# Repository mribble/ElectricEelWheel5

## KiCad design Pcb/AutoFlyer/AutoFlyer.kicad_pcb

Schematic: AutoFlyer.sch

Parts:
C1, C2, C3: 10uF; C_1206
C5: 0.1uF; C_0603
D1: LED_ALT; LED_0805
D3: D_Schottky; D_SOD-523
J1: Screw_Terminal_1x02; Socket_Strip_Straight_1x02_Pitch2.54mm
J2: Programmer; Socket_Strip_Straight_1x06_Pitch2.54mm
J3: Battery; Socket_Strip_Straight_1x04_Pitch2.54mm
R1: 1K; R_0603
R2: 10K; R_0603
R3: 0.5; R_0805
SW1: SW_Push; SW_SPST_PTS645
U1: ATTINY44-20SSU; SOIC-14_3.9x8.7mm_Pitch1.27mm
U2: LD1117S33TR_SOT223; SOT-23
U3: H-Bridge-DMHC3025LSD; SOIC-8-N
X1, X2: HOLE; HOLE_3.0mm

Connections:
+3V3: C2.1, C5.1, J2.3, SW1.2, U1.1 (VCC), U2.2 (VO)
+6V: C3.1, D3.2, J3.4, U3.7
/MotorA: J1.1, U3.2
/MotorB: J1.2, U3.6
/c0: U1.6 ((PCINT7/ICP/OC0B/ADC7)PA7), U3.1
/c1: U1.5 ((PCINT10/CKOUT/OC0A/INT0)PB2), U3.4
/c2: U1.3 ((PCINT9/XTAL2)PB1), U3.5
/c3: U1.2 ((PCINT8/CLKI/XTAL1)PB0), U3.8
/led: D1.2, U1.11 ((PCINT2/AIN1/ADC2)PA2)
/miso: J2.4, U1.8 ((PCINT5/DO/MISO/OC1B/ADC5)PA5)
/mosi: J2.5, U1.7 ((PCINT6/SDA/DI/MOSI/OC1A/ADC6)PA6)
/rst: J2.6, U1.4 ((PCINT11/dW/~RESET~)PB3)
/sck: J2.2, U1.9 ((PCINT4/USCK/SCL/T1/ADC4)PA4)
/shunt: R3.1, U1.13 ((PCINT0/AREF/ADC0)PA0), U3.3
GND: C1.2, C2.2, C3.2, C5.2, J2.1, J3.1, R1.1, R2.1, R3.2, U1.14 (GND), U2.1 (GND)
unnamed: C1.1, D3.1, U2.3 (VI)
unnamed: D1.1, R1.2
unnamed: J3.2, J3.3
unnamed: R2.2, SW1.1, U1.12 ((PCINT1/AIN0/ADC1)PA1)

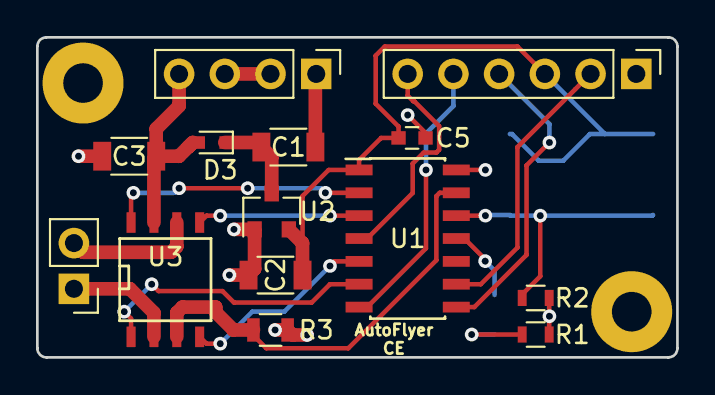
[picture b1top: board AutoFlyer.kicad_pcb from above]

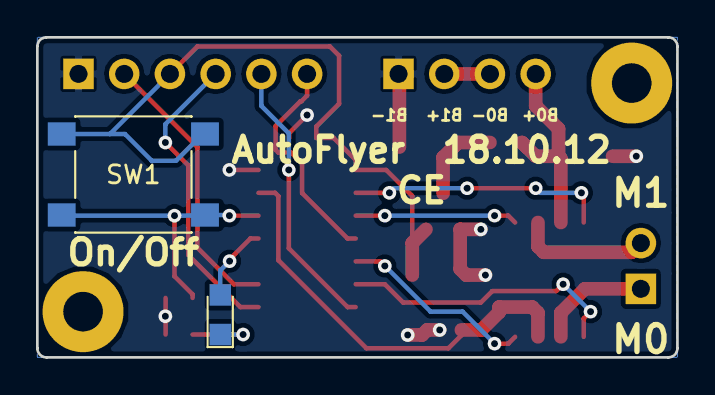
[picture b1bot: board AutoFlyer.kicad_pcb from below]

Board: 2 copper layers, 35.6 x 17.8 mm, 18 parts (2 on the bottom side), 19 nets.

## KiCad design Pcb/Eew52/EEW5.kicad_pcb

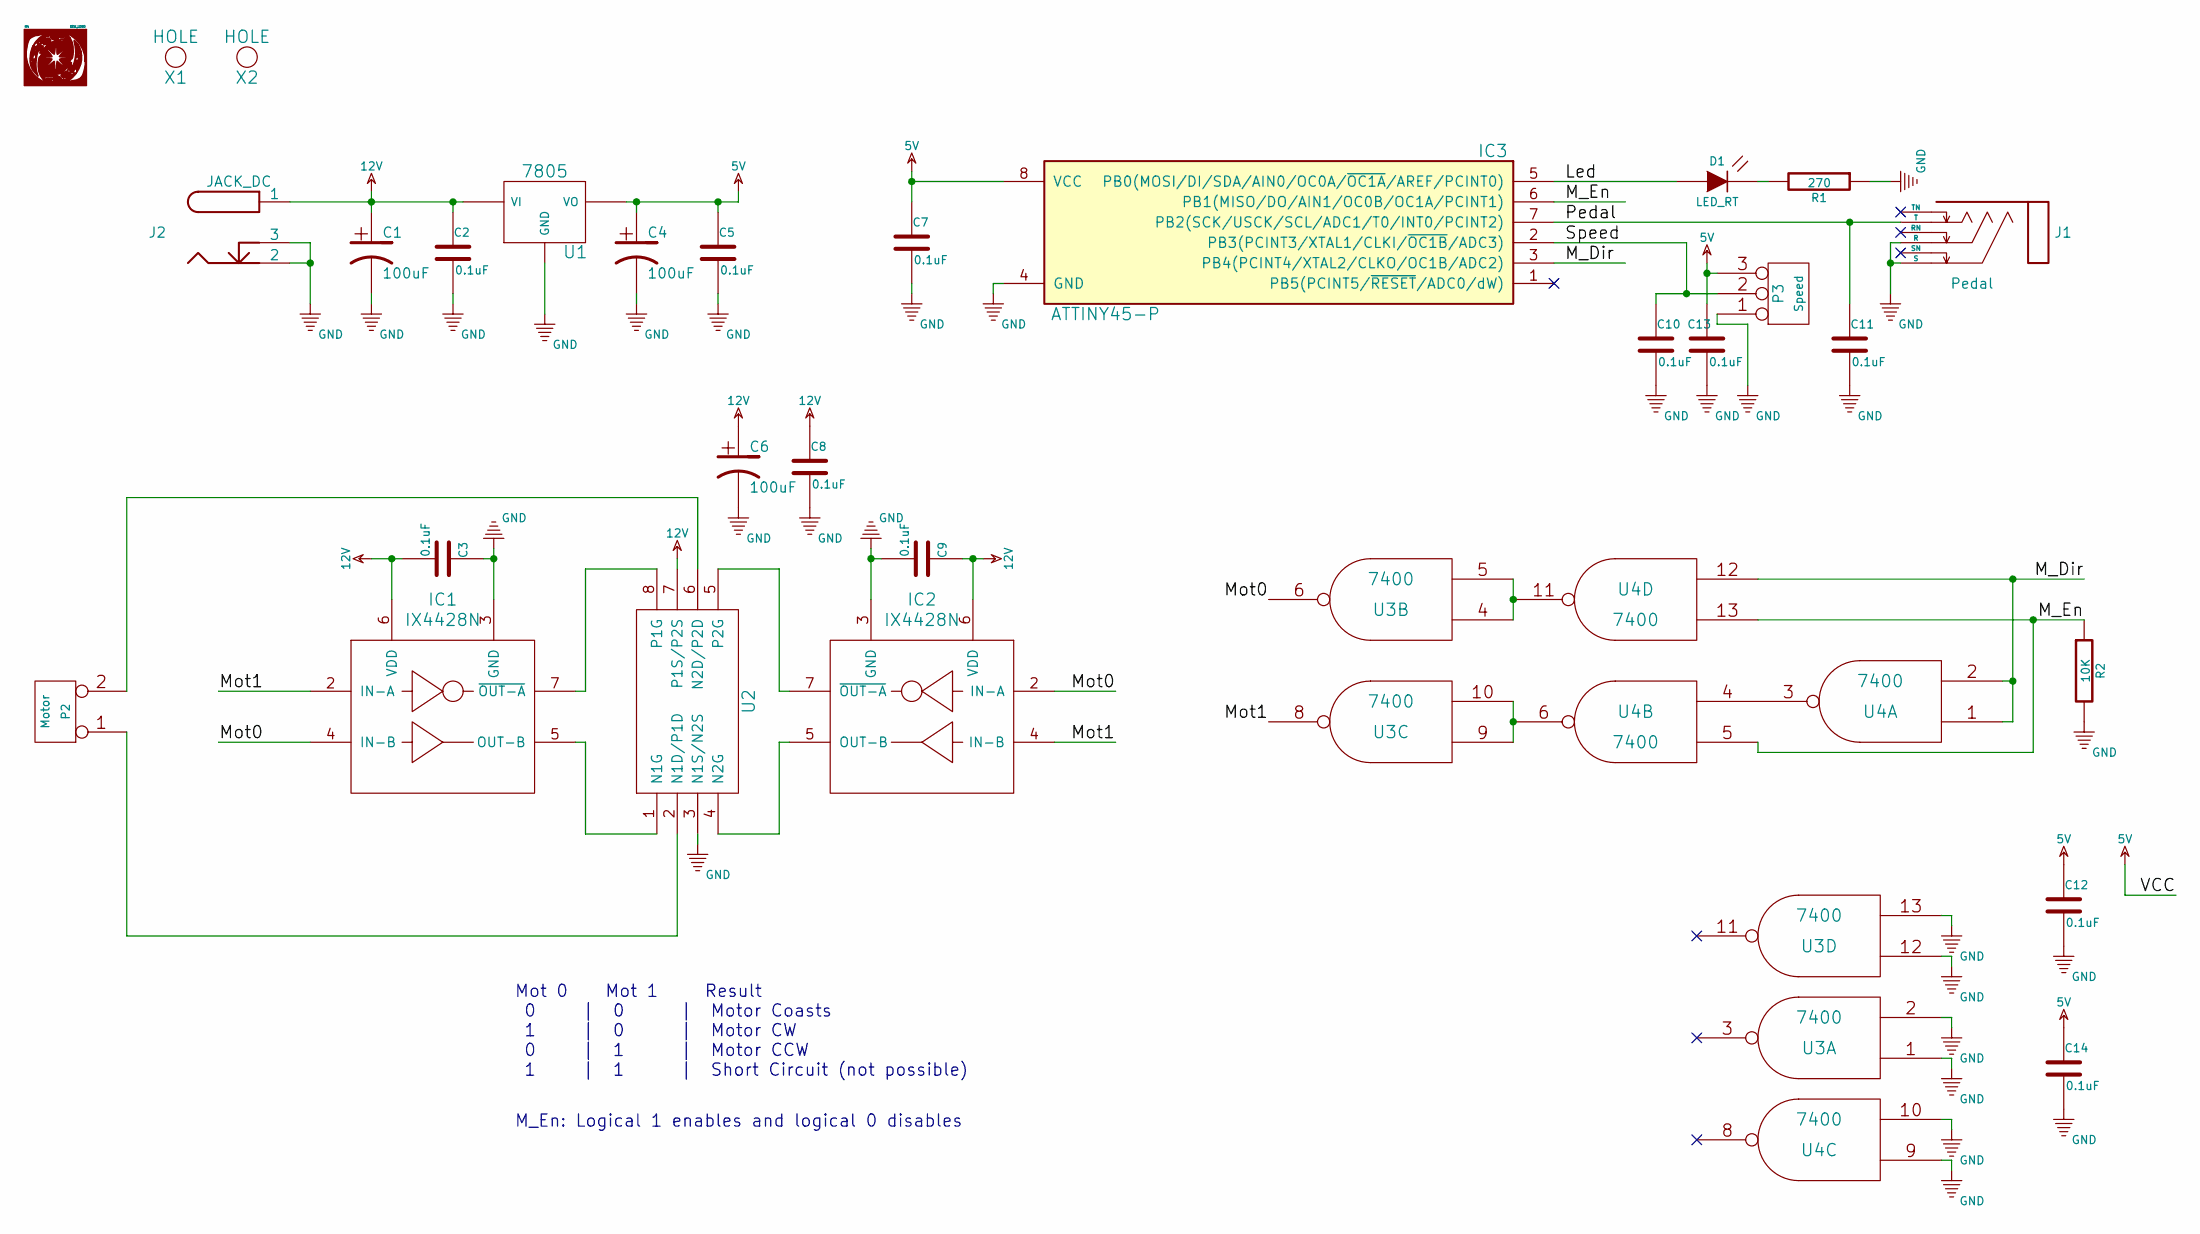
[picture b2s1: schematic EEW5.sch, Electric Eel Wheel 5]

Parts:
C1, C4, C6: 100uF; CP_Elec_6.3x5.7
C2, C3, C5, C7, C8, C9, C10, C11, C12, C13, C14: 0.1uF; C_0603
D1: LED_RT; LED_D5.0mm_Horizontal_O1.27mm_Z3.0mm
H4: EEW_LOGO; ce
IC1, IC2: IX4428N; SOIC-8-N
IC3: ATTINY45-P; DIP-8_W7.62mm_Socket
J1: Pedal; Jack_1_4
J2: JACK_DC; BARREL_JACK
P2: Motor; PhoenixContact_MC-G_02x3.50mm_Angled
P3: Speed; JST_EH_S03B-EH_03x2.50mm_Angled
R1: 270; R_0603
R2: 10K; R_0603
U1: 7805; TO-252-2
U2: H-Bridge-DMHC3025LSD; SOIC-8-N
U3, U4: 7400; SOIC-14_N
X1, X2: HOLE; HOLE_3.0mm

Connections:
5V: C4.1 (Pos), C5.1, C7.1, C12.1, C13.1, C14.1, IC3.8 (VCC), P3.3, U1.3 (VO), U3.14 (VCC), U4.14 (VCC)
12V: C1.1 (Pos), C2.1, C3.2, C6.1 (Pos), C8.1, C9.1, IC1.6 (VDD), IC2.6 (VDD), J2.1, U1.1 (VI), U2.7 (P1S/P2S)
/Led: D1.1 (A), IC3.5 (PB0(MOSI/DI/SDA/AIN0/OC0A/~OC1A~/AREF/P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)
/M_Dir: IC3.3 (PB4(PCINT4/XTAL2/CLKO/OC1B/ADC2)), U4.1, U4.2, U4.12
/M_En: IC3.6 (PB1(MISO/DO/AIN1/OC0B/OC1A/PCINT1)), R2.1, U4.5, U4.13
/Mot0: IC1.4 (IN-B), IC2.2 (IN-A), U3.6
/Mot1: IC1.2 (IN-A), IC2.4 (IN-B), U3.8
/Pedal: C11.1, IC3.7 (PB2(SCK/USCK/SCL/ADC1/T0/INT0/PCINT2)), J1.T
/Speed: C10.1, IC3.2 (PB3(PCINT3/XTAL1/CLKI/~OC1B~/ADC3)), P3.2
GND: C1.2 (Neg), C2.2, C3.1, C4.2 (Neg), C5.2, C6.2 (Neg), C7.2, C8.2, C9.2, C10.2, C11.2, C12.2, C13.2, C14.2, IC1.3 (GND), IC2.3 (GND), IC3.4 (GND), J1.R, J1.S, J2.2, J2.3, P3.1, R1.1, R2.2, U1.2 (GND), U2.3 (N1S/N2S), U3.1, U3.2, U3.7 (GND), U3.12, U3.13, U4.7 (GND), U4.9, U4.10
unnamed: D1.2 (K), R1.2
unnamed: IC1.5 (OUT-B), U2.1 (N1G)
unnamed: IC1.7 (~OUT-A), U2.8 (P1G)
unnamed: IC2.5 (OUT-B), U2.4 (N2G)
unnamed: IC2.7 (~OUT-A), U2.5 (P2G)
unnamed: P2.1, U2.2 (N1D/P1D)
unnamed: P2.2, U2.6 (N2D/P2D)
unnamed: U3.4, U3.5, U4.11
unnamed: U3.9, U3.10, U4.6
unnamed: U4.3, U4.4

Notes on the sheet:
Mot 0 Mot 1 Result 0 | 0 | Motor Coasts 1 | 0 | Motor CW 0 | 1 | Motor CCW 1 | 1 | Short Circuit (not possible)
M_En: Logical 1 enables and logical 0 disables

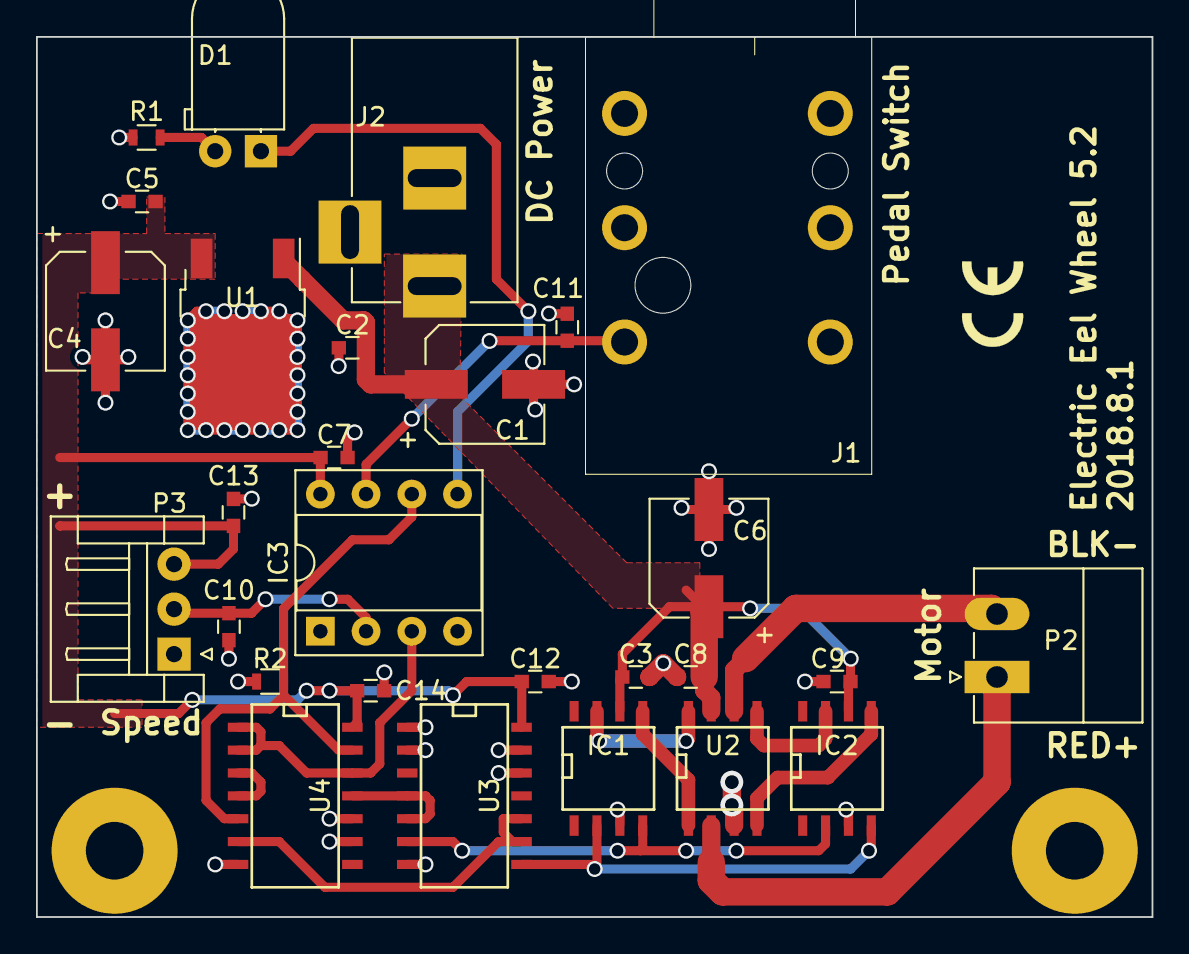
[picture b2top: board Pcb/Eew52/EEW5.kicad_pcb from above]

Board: 2 copper layers, 62.0 x 48.9 mm, 31 parts (0 on the bottom side), 20 nets.

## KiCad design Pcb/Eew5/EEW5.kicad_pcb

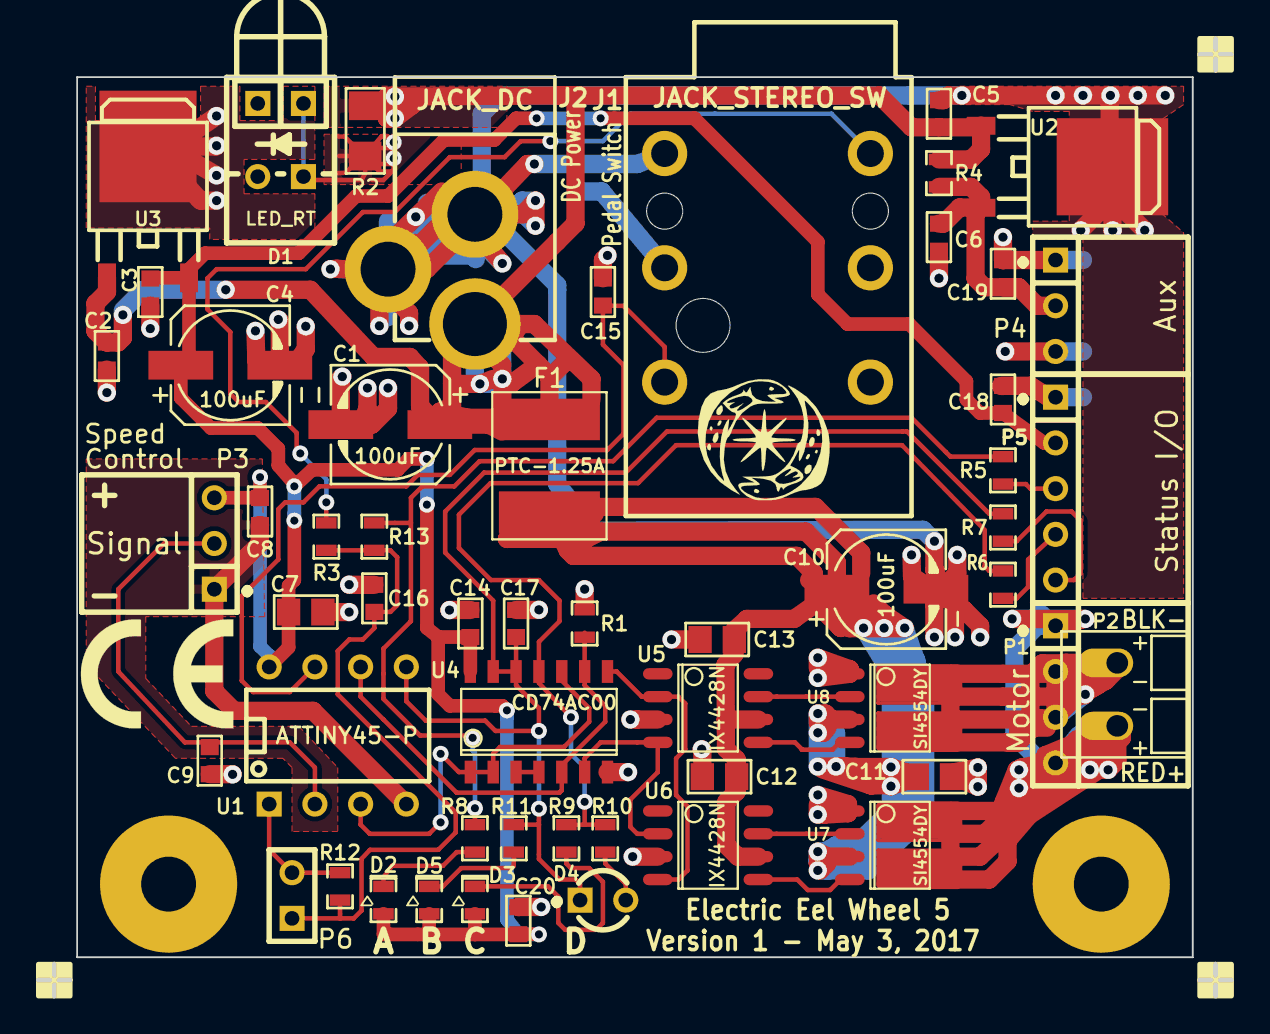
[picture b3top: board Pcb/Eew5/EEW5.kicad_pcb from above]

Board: 2 copper layers, 66.3 x 53.2 mm, 60 parts (0 on the bottom side), 32 nets.

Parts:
C1, C4, C10: 100uF; c_elec_6.3x5.7
C2, C3, C5, C6, C8, C9, C14, C15, C16, C17, C18, C19, C20: 0.1uF; c_0603
C7, C11, C12, C13: 1uF; c_0805
D1: LED_RT; LED_RT_100
D2, D3: Green; SM0603_Diode
D4: R/G; LED_T1_BiPolar_100
D5: Red; SM0603_Diode
F1: PTC-1.25A; PTC_2920
J1: JACK_STEREO_SW; JACK_1-4_STEREO
J2: JACK_DC; JACK_2.1_DC
P1: Motor; SIL-4-RT
P2: Motor; Screw_Terminal_Block_2P
P3: Speed; SIL-3-RT
P4: Aux; SIL-3-RT
P5: Status I/O; SIL-5-RT
P6: R/PE; SIL-2
PS1, PS2: CONN_1; SIL-1
R1: 10k; SM0603_Resistor
R2: 820; r_1206
R3, R4, R12, R13: 0k; SM0603_Resistor
R5, R6, R7, R8, R9, R10, R11: 270; SM0603_Resistor
U1: ATTINY45-P; DIP-8_300
U2: KA78xxE; TO252M
U3: KA7805E; TO252M
U4: CD74AC00; SOIC-14
U5, U6: IX4428N; SOIC-8
U7, U8: SI4554DY; SO-8P2
X1, X2: HOLE; HOLE_4-40
ref***: val***; EEW_Logo_small

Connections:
5V: C3.1, C4.1, C7.1, C8.2, C14.1, C18.1, C20.1, D2.1, D3.1, D5.1, P3.3, P5.2, U1.8, U3.VO, U4.14
/AuxPwr: C6.1, C19.1, P4.2, R4.2, U2.VO
/CCW_LS: U6.7, U7.2
/CW_LS: U5.7, U8.2
/DC_In: C1.1, C2.1, C5.1, F1.2, J2.1, R2.1, R4.1, U2.VI, U3.VI
/HPWR: C10.1, C11.1, C12.2, C13.2, F1.1, U5.6, U6.6, U7.3, U8.3
/M+: P1.1, P1.4, P2.1, U7.5, U7.6, U7.7, U7.8
/M-: P1.2, P1.3, P2.2, U8.5, U8.6, U8.7, U8.8
/M_DIR: U1.3, U4.1, U4.2, U4.10
/M_EN: R1.1, U1.6, U4.5, U4.9
/PEn_x: C16.1, P6.1, R3.1, R12.2, R13.2
/PEn_y: J1.SN, R3.2
/PEn_z: R5.2, R8.1, R13.1
/PedalEnable: P6.2, R12.1, U1.1
/PedalSig: C15.1, J1.T, U1.7
/Speed: C9.2, P3.2, U1.2
/Status: C17.1, D4.1, R7.2, R11.1, U1.5, U4.12, U4.13
/~CCW: U4.6, U5.4, U6.2
/~CCW_HS: U5.5, U8.4
/~CW: U4.8, U5.2, U6.4
/~CW_HS: U6.5, U7.4
/~M_DIR: U4.3, U4.4
/~Status: R6.2, R9.1, R10.1, U4.11
GND: C1.2, C2.2, C3.2, C4.2, C5.2, C6.2, C7.2, C8.1, C9.1, C10.2, C11.2, C12.1, C13.1, C14.2, C15.2, C16.2, C17.2, C18.2, C19.2, C20.2, D1.2, J1.R, J1.S, J2.2, J2.3, P3.1, P4.1, P4.3, P5.1, PS2.1, R1.2, U1.4, U2.GND, U3.GND, U4.7, U5.3, U6.3, U7.1, U8.1
unnamed: D2.2, R8.2
unnamed: P5.4, R6.1
unnamed: D3.2, R9.2
unnamed: D5.2, R11.2
unnamed: D4.2, R10.2
unnamed: D1.1, PS1.1, R2.2
unnamed: P5.3, R5.1
unnamed: P5.5, R7.1

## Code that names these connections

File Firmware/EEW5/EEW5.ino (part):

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// 1.01 Sep 8, 2015 - Nedd
//      - Simplified some math lines to improve loop speed
//      - Increased system clock to 16mhz (was 1mhz). This improves the resolution of the micros() counter, reduces signal jitter, allows faster PWM frequencies.
//      - Added "TESTMODE" for repeated LV programming during testing. (In TESTMODE fuse RSTDISBL is unprogrammed, Reset (pin 1) is open, PB0 (pin 5) is rewired to M_EN, 
//        MOT_EN_PIN & PEDAL_EN_PIN definitions are swapped).
// 1.02 Oct 31, 2015 - Maurice Ribble
//      - Reduced math by pre-caching high and low speed
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//      - Added Fwd/Rev testing for new pcb MOSFET drive system.
//      - Testing of old PWM method using new prototype PCB design, (version 6).
// 1.05 Feb 02, 2016 - Nedd
//      - Added register setups to use direct PWM output on PB1, PWM comes from OC1A signal, PW is adjusted by setting OCR1A (compare A) of timer1.
//      - Added Dead Zone adjustment (expands range where motor is at 0 speed)
//      - Added Slow Zone adjustment (reduces range where motor does not spin)
//      - Added safe mode at first power on. Operator must adjust speed knob up then back to zero to enable motor. Status line toggles detection points
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// Digital/analog pins
#define PIN_STATUS            0    // Green status LED output     -- LOW=On       HIGH=Off
#define PIN_MOT_EN            1    // Enable motor output         -- LOW=Stop     HIGH=Run
#define PIN_PEDAL             2    // Foot pedal switch input     -- LOW=Pressed  HIGH=Not Pressed
#define APIN_SPEED            3    // Speed control dial analog input (ADC3 = PB3)
#define PIN_MOT_DIR           4    // Direction motor output      -- LOW=CCW      HIGH=CW

// Green Status LED
#define LED_ON  LOW
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
// Speed dial related controls
#define DEAD_ZONE 15               // Range close to zero where motor will be forced off
#define SLOW_ZONE 90               // Shift motor's minimum speed faster to get motor spinning at lower speed dial settings
#define T1_MAX_TIME 168            // Used to help set pwm durations, see setPwmParams() for more details

////////////////////////////////////////////////////////////////////////////////////////////////////////////////////////
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}

////////////////////////////////////////////////////////////////////////////////////////////////////////////////////////
// analogReadSpeedDial - Fast readAnalog for the pin connected to the speed dial
//  input   - void
//  return  - 8 bit analog value
////////////////////////////////////////////////////////////////////////////////////////////////////////////////////////
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////////////////////////////////////////////////////////////////////////////////////////////////////////////////////////
inline void motorPwmOff()
{
  TCCR1 &= ~(1<<COM1A1);  TCCR1 &= ~(1<<COM1A0);  //disconnect pwm from PB1
}  

////////////////////////////////////////////////////////////////////////////////////////////////////////////////////////
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inline void motorPwmOn()
{ 
  TCCR1 |= (1<<COM1A1);  
  TCCR1 |= (1<<COM1A0);  //connect pwm to PB1
}

////////////////////////////////////////////////////////////////////////////////////////////////////////////////////////
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  ADCSRA |=  (1<<ADEN)  ;  // 1, ADC Enable
   
  //ADMUX, ADC Mux Seletion Register
  ADMUX |=  (1<<MUX0);   // 1, adc Mux channel (ADMUX bits MUX[3-0], for ADC3(PB3) single ended need "B0011")
  ADMUX |=  (1<<MUX1);   // 1
  ADMUX &= ~(1<<MUX2);   // 0
  ADMUX &= ~(1<<MUX3);   // 0
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}

////////////////////////////////////////////////////////////////////////////////////////////////////////////////////////
// setPwmParams - Sets up PWM parameters for motor.  Must be called before using the pwm from PB1
////////////////////////////////////////////////////////////////////////////////////////////////////////////////////////
void setPwmParams()
{
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  // Disable motor enable pin 
  digitalWrite(PIN_MOT_EN, LOW);

  // Setup pwm registers for output on PB1 using the timer counter 1
  // Temporarily stop counters by setting Timer Sync Mode bit to 1 
  GTCCR |=  (1<<TSM);
  // Place Timer1 into Reset by setting Timer1 Prescaler to 1
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  // set up all 8-bits of TCCR1, (Timer/Counter1 Control Register)
  // set CTC1 to 1,(Clear Timer/Counter on Compare), this will clear timer1 to 0x00 on match of 0CR1C (maxCnt)   
  // set PWM1A to 1, (PWM A enable), this enables pwm based on match of 0CR1A   
  // set COM1A0 & COM1A0 to 3, (compare A output mode), this connects 0C1A to PB1, and the output will be set on a CMP A.  (PB1 must be set as an output)
  // set CS13,CS12,CS11,CS10 to 3, (timer1 prescaler) this selects TCK1/4
  TCCR1 = 1<<CTC1 | 1<<PWM1A | 3<<COM1A0 | 3<<CS10;
  
  // GTCCR,(General Timer Counter Control Register), setup/disable other timer counter 1 items
  // set PWM1B to 0, this will disable PWM1B
  // set COM1B1 & COM1B0 to 0x00, this will disable the connection of 0C1B to PB4
  GTCCR &= ~(1<<PWM1B);
  GTCCR &= ~(1<<COM1B0);
  GTCCR &= ~(1<<COM1B1);
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   
  // interupts for timer1 should already be cleared as a default.
   
  // To achieve a specific PWM on PB1: 
  // Adjust OCR1A from T1_MAX_TIME to 0x00, with T1_MAX_TIME for 100% off, and 0x00 for 100% on.
}

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  pinMode(PIN_MOT_EN,  OUTPUT);
  pinMode(PIN_MOT_DIR, OUTPUT);
  pinMode(PIN_STATUS,  OUTPUT);
  pinMode(PIN_PEDAL,   INPUT_PULLUP);

#ifdef ENABLE_BI_LED
  setBiLedStatus(BI_LED_RED);
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
  motorSpeed = (motorSpeed < DEAD_ZONE) ? 0 : motorSpeed;

  if (digitalRead(PIN_PEDAL) == LOW)    // If pedel is pressed
  {
    digitalWrite(PIN_STATUS, LED_OFF);  // Make sure status led is off
    pedalOn = !pedalOn;                 // Toggle pedal press state
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    do  // Debounce
    { 
      delay(10);
    } while(digitalReadFast(PIN_PEDAL) == LOW);
  }

  // By forcing pedalOn when speed is 0 the wheel can be started without a pedal by turning speed to 0
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    }
    else
    {
      digitalWrite(PIN_MOT_DIR, LOW);  // Set motor direction to ccw
    }
  }

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
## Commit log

2017-02-23 Add EEW5 case to git
2017-03-16 Fix bug with motor direction when using the foot pedal and unplugging the EEW5
2017-04-05 Add documentation and various tools
2017-04-05 Add spin card and spin key
2017-04-05 Rename Docs to Documentation
2017-04-19 Add Niddy Noddy Card files
2017-05-03 Update silkscreen with ce logo
2017-05-04 Fix part label on silkscreen
2017-07-12 Add Lazy Kate instruction Card and add LED timeout
2017-11-30 Update include card
2017-12-26 Remove bobbin bit from manual
2018-05-31 Sync files (no change)
2018-08-01 Fixed bug in layout. Also uploaded autoflyer and new firmware for eew 5.2
2018-10-11 Add autoflyer pcb
2019-04-03 Update auto flyer and some documentation
2019-05-30 Update lib

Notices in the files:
Firmware/EEW5/EEW5.ino:
Open Source, licensed under Creative Commons Attribution 3.0 License (http://creativecommons.org/licenses/by-sa/3.0/)
